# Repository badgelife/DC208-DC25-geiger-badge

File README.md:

DEF CON 25 DC208 Geiger Badge
========================

Repo Format
-----------
kicad folder is the schematic and board files

firmware folder contains firmware for the project. Check out the doc folder for design and how to flash the chip.

Contributing
------------
### Schematic Changes
Please limit changes to schematic as one task per commit with relevant commit messages.

### Firmware Changes
Please perform all firmware updates on a branch, and open a pull request to merge the changes to master once they're 
tested and complete. This will help keep master in a good state.

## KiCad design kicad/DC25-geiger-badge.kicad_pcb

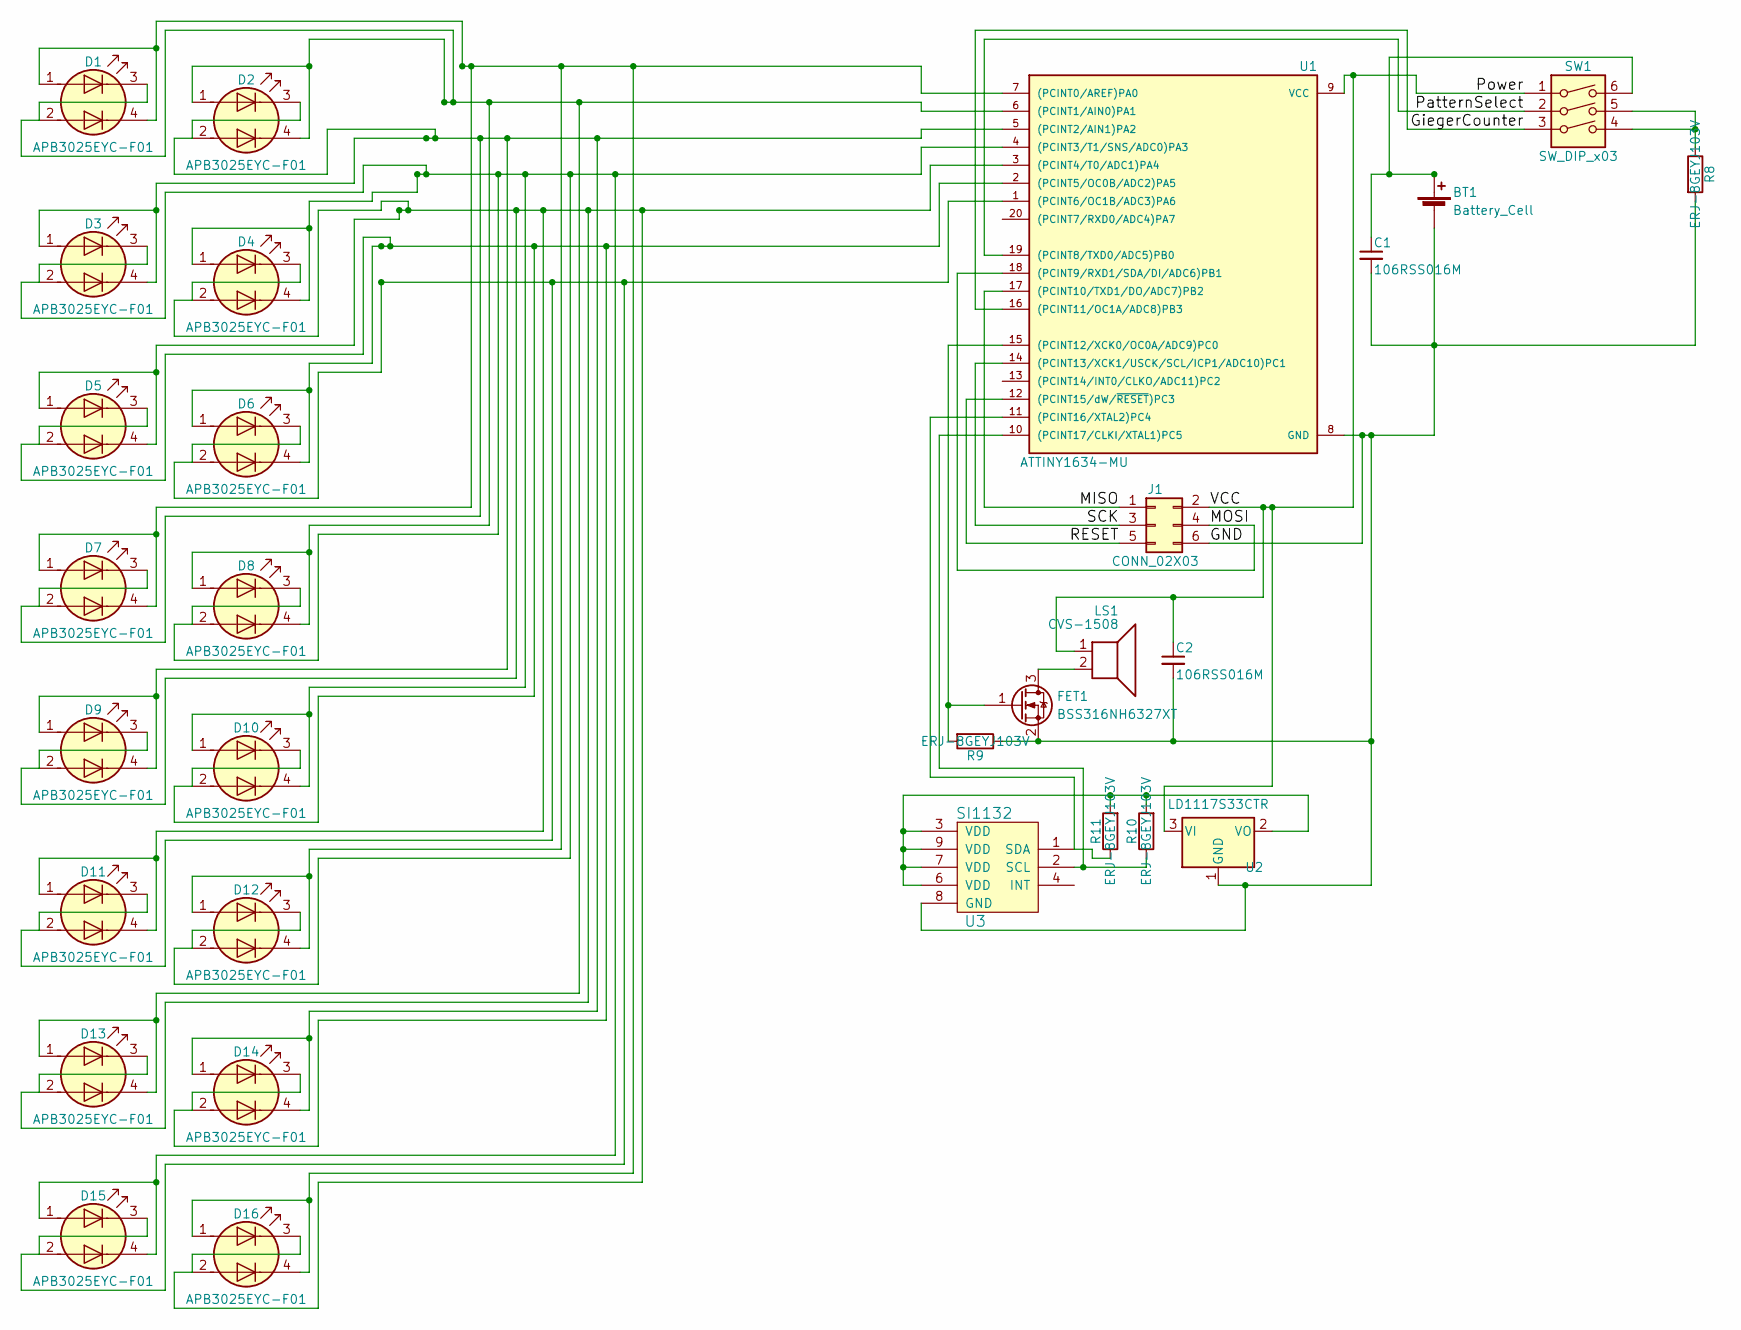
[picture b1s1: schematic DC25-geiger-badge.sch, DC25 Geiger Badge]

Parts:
BT1: Battery_Cell; Molex_MicroLatch-53254-0270_02x2.00mm_Angled
C1, C2: 106RSS016M; CP_Radial_D4.0mm_P1.50mm
D1, D2, D3, D4, D5, D6, D7, D8, D9, D10, D11, D12, D13, D14, D15, D16: APB3025EYC-F01; LED_SMD_3225-4pin_3.2x2.5mm
FET1: BSS316NH6327XT; SOT-23
J1: CONN_02X03; Pin_Header_Straight_2x03_Pitch2.54mm
LS1: CVS-1508; SPK1
R8, R9, R10, R11: ERJ-8GEYJ103V; R_1206
SW1: SW_DIP_x03; DIP-6_W7.62mm_LongPads
U1: ATTINY1634-MU; QFN-20-1EP_4x4mm_Pitch0.5mm
U2: LD1117S33CTR; SOT-223
U3: SI1132; QFN-10-SI1132

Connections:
/GND: BT1.2 (-), C1.2, C2.2, FET1.2 (S), J1.6, R8.2, R9.1, U1.8 (GND), U2.1 (GND), U3.8 (GND)
/GiegerCounter: SW1.3, U1.16 ((PCINT11/OC1A/ADC8)PB3)
/MISO: J1.1, U1.17 ((PCINT10/TXD1/DO/ADC7)PB2)
/MOSI: J1.4, U1.18 ((PCINT9/RXD1/SDA/DI/ADC6)PB1)
/PatternSelect: SW1.2, U1.19 ((PCINT8/TXD0/ADC5)PB0)
/Power: C2.1, J1.2, LS1.1, SW1.1, U1.9 (VCC), U2.3 (VI)
/RESET: J1.5, U1.12 ((PCINT15/dW/~RESET~)PC3)
/SCK: J1.3, U1.14 ((PCINT13/XCK1/USCK/SCL/ICP1/ADC10)PC1)
unnamed: BT1.1 (+), C1.1, SW1.6
unnamed: D1.1 (A1), D1.4 (K2), D7.1 (A1), D7.4 (K2), D12.1 (A1), D12.4 (K2), D16.1 (A1), D16.4 (K2), U1.7 ((PCINT0/AREF)PA0)
unnamed: D1.2 (A2), D1.3 (K1), D2.1 (A1), D2.4 (K2), D8.1 (A1), D8.4 (K2), D13.1 (A1), D13.4 (K2), U1.6 ((PCINT1/AIN0)PA1)
unnamed: D3.2 (A2), D3.3 (K1), D4.1 (A1), D4.4 (K2), D8.2 (A2), D8.3 (K1), D10.1 (A1), D10.4 (K2), D12.2 (A2), D12.3 (K1), D15.1 (A1), D15.4 (K2), U1.4 ((PCINT3/T1/SNS/ADC0)PA3)
unnamed: D5.2 (A2), D5.3 (K1), D6.1 (A1), D6.4 (K2), D10.2 (A2), D10.3 (K1), D14.2 (A2), D14.3 (K1), U1.2 ((PCINT5/OC0B/ADC2)PA5)
unnamed: D4.2 (A2), D4.3 (K1), D5.1 (A1), D5.4 (K2), D9.2 (A2), D9.3 (K1), D11.1 (A1), D11.4 (K2), D13.2 (A2), D13.3 (K1), D16.2 (A2), D16.3 (K1), U1.3 ((PCINT4/T0/ADC1)PA4)
unnamed: D6.2 (A2), D6.3 (K1), D11.2 (A2), D11.3 (K1), D15.2 (A2), D15.3 (K1), U1.1 ((PCINT6/OC1B/ADC3)PA6)
unnamed: D2.2 (A2), D2.3 (K1), D3.1 (A1), D3.4 (K2), D7.2 (A2), D7.3 (K1), D9.1 (A1), D9.4 (K2), D14.1 (A1), D14.4 (K2), U1.5 ((PCINT2/AIN1)PA2)
unnamed: FET1.1 (G), R9.2, U1.15 ((PCINT12/XCK0/OC0A/ADC9)PC0)
unnamed: FET1.3 (D), LS1.2
unnamed: R8.1, SW1.4, SW1.5
unnamed: R10.1, U1.10 ((PCINT17/CLKI/XTAL1)PC5), U3.2 (SCL)
unnamed: R10.2, R11.2, U2.2 (VO), U3.3 (VDD), U3.6 (VDD), U3.7 (VDD), U3.9 (VDD)
unnamed: R11.1, U1.11 ((PCINT16/XTAL2)PC4), U3.1 (SDA)

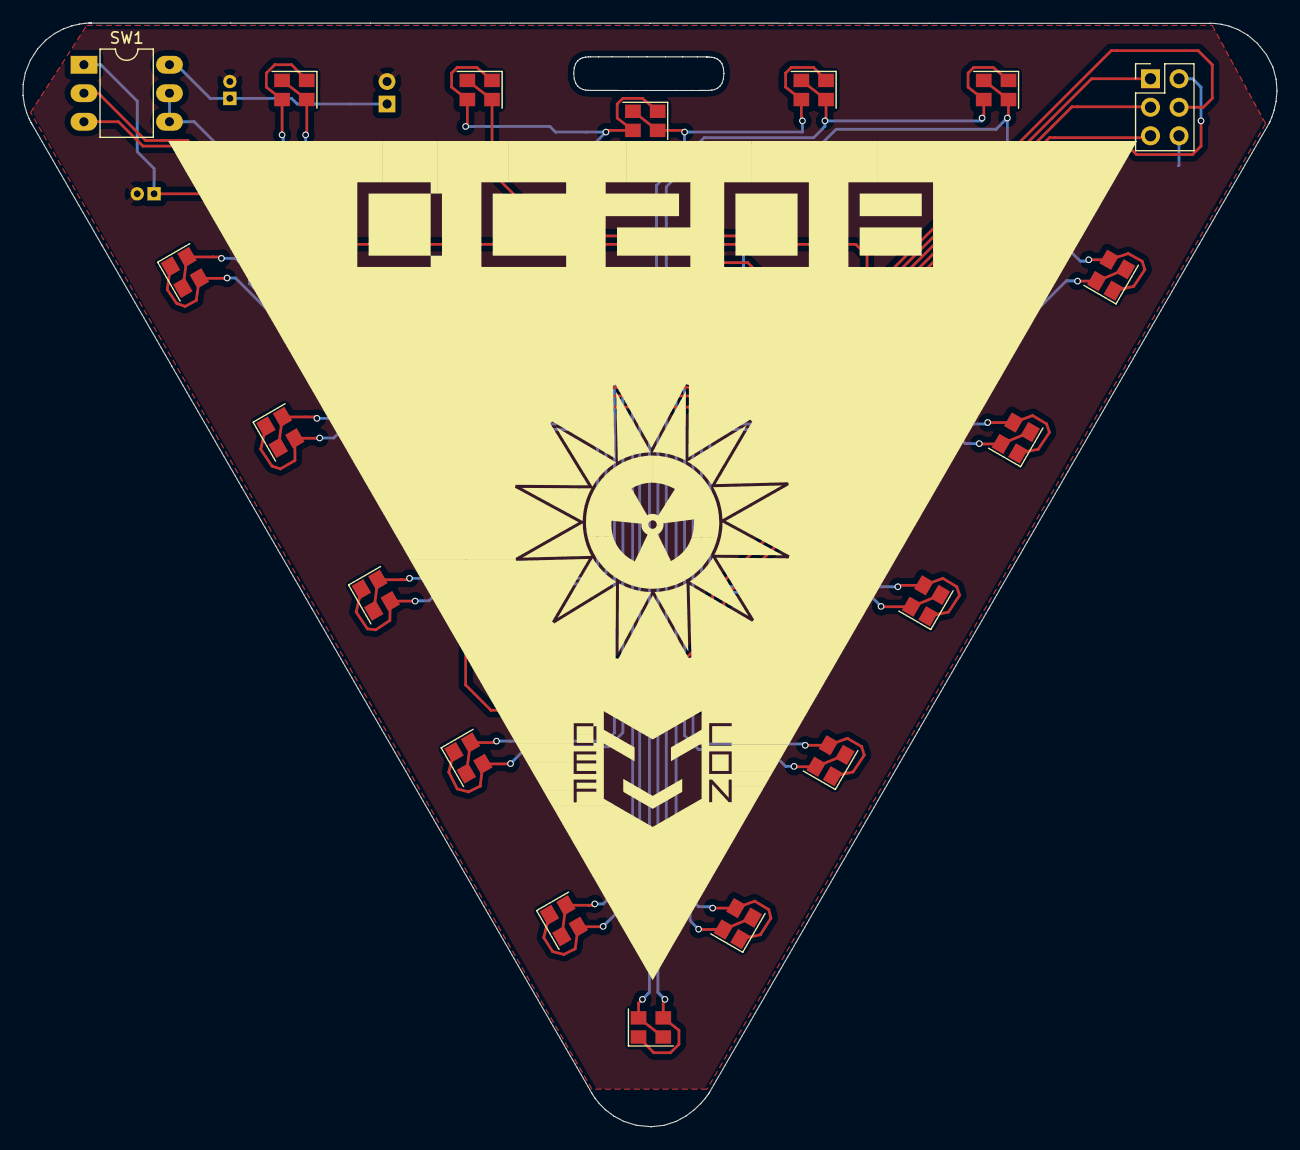
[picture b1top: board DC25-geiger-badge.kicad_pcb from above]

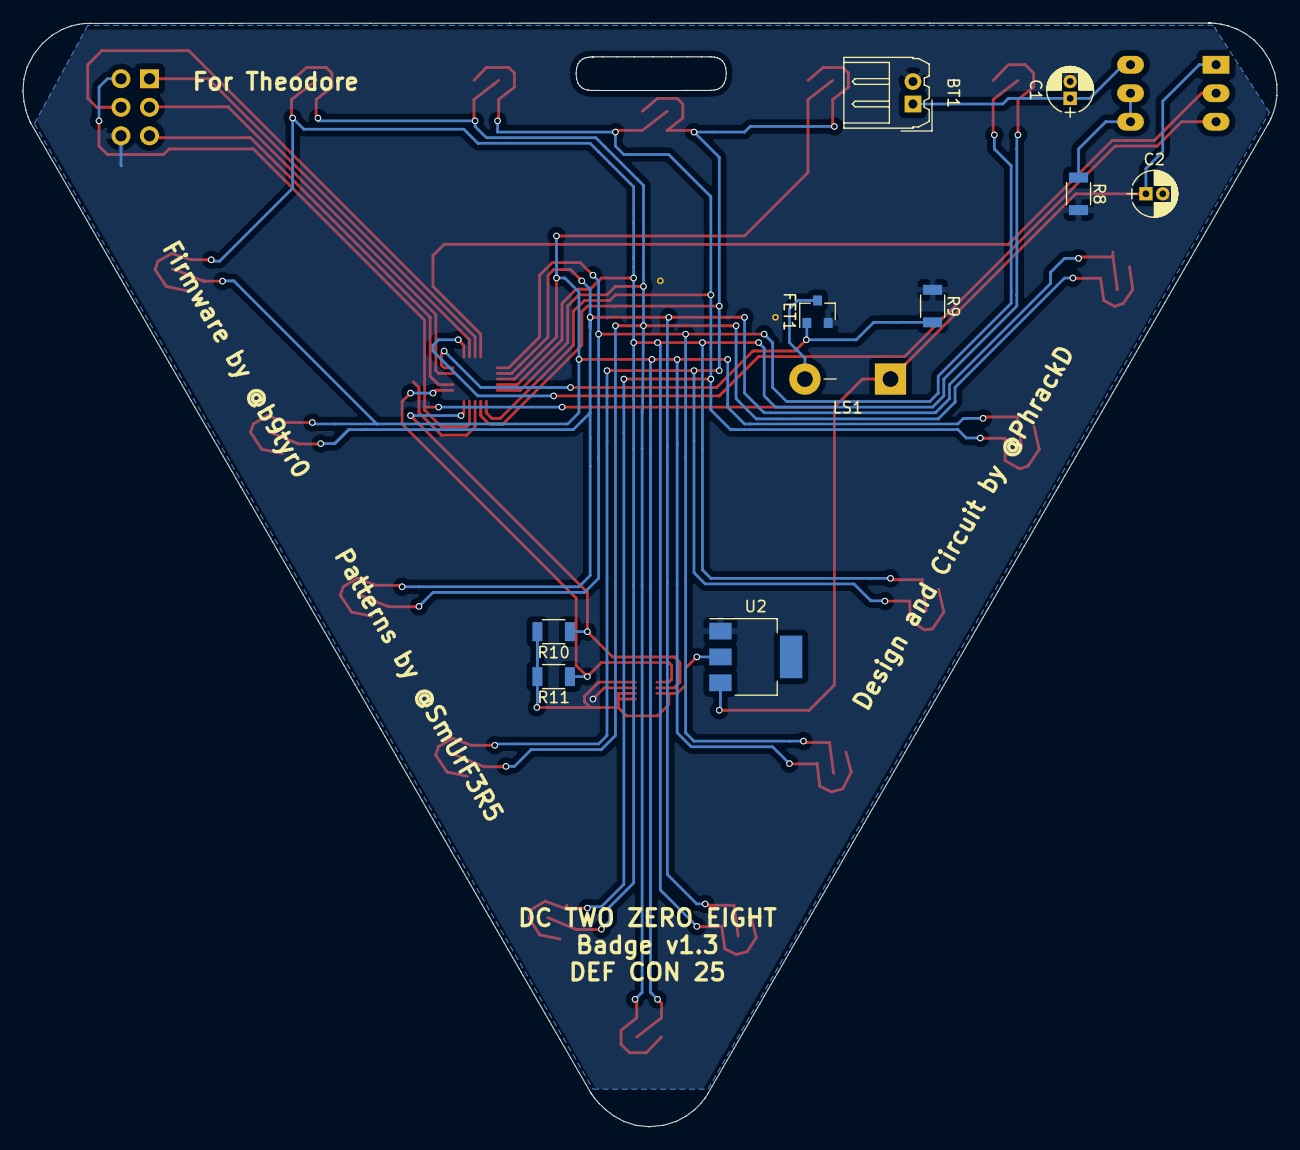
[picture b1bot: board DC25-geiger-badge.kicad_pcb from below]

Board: 2 copper layers, 111.7 x 98.3 mm, 31 parts (10 on the bottom side), 22 nets.

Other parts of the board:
svg2mod: G***; dc208SilkScreen

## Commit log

2017-11-20 add license
2017-11-20 add rev1.3 schematic and pcb
2017-11-20 add readme and example image
2017-11-20 add patterns and tool
2017-11-20 add firmware docs
